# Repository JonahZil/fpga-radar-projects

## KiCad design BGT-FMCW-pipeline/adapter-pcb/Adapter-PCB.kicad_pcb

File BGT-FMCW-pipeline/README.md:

# FPGA FMCW Radar Pipeline

This project implements a complete real-time radar system using an Infineon BGT60TR13C shield radar sensor and a Xilinx Zynq-7000 SoC. The radar detects the strongest object in front of it, calculates its distance and direction on the FPGA, and sends the resulting 3D position to a Python application for visualization. The demonstration below shows the system tracking a moving corner reflector.

## Overview

The complete processing chain is:

BGT60TR13C
    -> Radar configuration
    -> SPI acquisition
    -> three-channel buffering
    -> Hann windowing
    -> three 256-point range FFTs, built from scratch
    -> strongest-target detection
    -> range and angle calculation
    -> AXI4-Lite
    -> Zynq processing system
    -> UART
    -> Python 3D visualization

Nearly all radar processing is performed in programmable logic. The processing system only reads the completed result and forwards it to the computer over UART.

## Hardware

The system consists of:

* Infineon BGT60TR13C 60 GHz FMCW radar shield
* Zybo Z7 with a Xilinx Zynq-7000 SoC
* Custom radar-to-PMOD adapter PCB
* Three radar receiver channels and one transmitter
* USB UART connection to the computer

The radar operates with 1.8 V logic, while the Zybo PMOD uses 3.3 V logic. The custom PCB uses two SN74AVC4T245 level translators and an AP2112K 1.8 V regulator to safely connect the boards. The adapter PCB is shown below:

## Radar Configuration

The FPGA configures the BGT60TR13C through SPI using register values stored in a ROM. It starts each frame, waits for the sensor FIFO interrupt, and performs a burst read of the ADC samples.

The current configuration uses:

* Three receiver channels
* 256 samples per receiver
* 768 ADC samples per frame
* 256-point range FFTs
* FFT bins 6 through 127 for target detection
* 37.5 mm of range per FFT bin
* A 100 MHz FPGA clock
* A frame period of approximately 16.7 ms
* An update rate of approximately 60 FPS

## Signal Processing

### Acquisition and Buffering

The BGT60TR13C produces interleaved 12-bit unsigned ADC samples from its three receiver channels. The FPGA reads the FIFO over SPI, separates the channels, subtracts the ADC midpoint of 2048, and stores each channel in BRAM.

### Hann Window

A 256-point Hann window is applied before each FFT to reduce spectral leakage. The coefficients are stored in ROM as unsigned Q0.12 values.

### Range FFT

A separate 256-point fixed-point FFT is calculated for each receiver. Only positive-frequency bins 6 through 127 are searched. The lowest bins are ignored because they primarily contain DC leakage and direct coupling. The FFT module was made from scratch in the previous project, found under the "simulated-FMCW-pipeline" repository.

### Peak Detection

For each candidate bin, the design calculates:

power = real^2 + imaginary^2

The power values from all three receivers are added together. The bin with the largest combined response is selected as the strongest target.

### Range Calculation

Range is calculated directly from the selected FFT bin:

range_um = peak_bin * 37,500

The FPGA outputs range as an unsigned 24-bit integer in micrometres.

### Angle Calculation

Azimuth and elevation are calculated from the phase differences between the complex FFT outputs of different receiver pairs.

The design:

1. Multiplies one receiver value by the complex conjugate of another
2. Uses a custom CORDIC atan2 module to calculate the phase difference
3. Applies experimentally measured boresight phase offsets
4. Uses an inverse-sine lookup table to calculate the final angle

Phase and angle values use signed radians scaled by 2^15.

The inverse-sine ROM discards seven least-significant phase bits before lookup:

lut_address = abs(corrected_phase) >> 7

This reduces the ROM to 805 entries while retaining angular resolution.

The final RTL outputs are:

output reg signed [17:0] alpha;
output reg signed [17:0] beta;
output reg        [23:0] range_calc;

* alpha is the azimuth in radians multiplied by 2^15
* beta is the elevation in radians multiplied by 2^15
* range_calc is the range in micrometres

## Data Transfer and Visualization

The completed results are exposed to the Zynq processing system through a custom AXI4-Lite peripheral using the Vivado AXI4-Lite template.

Embedded C software waits for a valid result, reads the three output registers, and sends them over UART at 921,600 baud.

Each packet contains:

uint32 range_um
int32  alpha_q15
int32  beta_q15

The Python application decodes the packet, converts the fixed-point values to metres and degrees, transforms the spherical coordinates into Cartesian coordinates, and updates a Matplotlib 3D display.

The current implementation displays one point because the FPGA returns only the strongest target.

## Fixed-Point Formats

The main fixed-point formats are:

* Raw ADC sample: 12-bit unsigned integer
* Centered ADC sample: signed integer
* Hann coefficient: unsigned Q0.12
* FFT input: 24-bit signed with 15 fractional bits
* FFT real and imaginary outputs: 24-bit signed
* Phase: signed radians multiplied by 2^15
* Azimuth and elevation: signed radians multiplied by 2^15
* Range: unsigned integer, micrometres

Intermediate calculations use wider values to prevent overflow before truncation.

## Main RTL Modules

* bgt_master: radar configuration and acquisition state machine
* spi_master: radar register transactions
* burst_spi_master: continuous FIFO burst reads
* config_rom: BGT60TR13C register configuration
* io_buffer: buffering and signal-processing control
* hann_rom: Hann-window coefficients
* sdf_fft: three 256-point range FFTs
* atan2_cordic: phase-difference calculation
* cordic_angle_rom: CORDIC constants
* asin_rom: phase-to-angle conversion
* AXI4-Lite slave: transfers completed results to the processing system

## FPGA Implementation

The design meets timing at 100 MHz with a worst negative slack of **+0.428 ns**.

Resource utilization:

* LUT: 5,689 used, 32%
* Flip-flops: 5,418 used, 15%
* BRAM: 14.5 blocks used, 24%
* DSP slices: 50 used, 63%

DSP slices are the most heavily used resource because of the FFTs, window multiplication, magnitude calculations, and complex phase arithmetic.

## Verification

The pipeline was verified using:

* RTL simulation
* Python and NumPy reference calculations
* Synthetic ADC signals with known frequencies and phase offsets
* Vivado ILA and VIO
* Comparison of FPGA FFT outputs with software FFTs
* Fixed-point range and angle comparisons
* Physical testing with a corner reflector
* Measurements at boresight and different target distances

The Python reference model reproduces the same fixed-point scaling and seven-bit phase truncation used by the RTL.

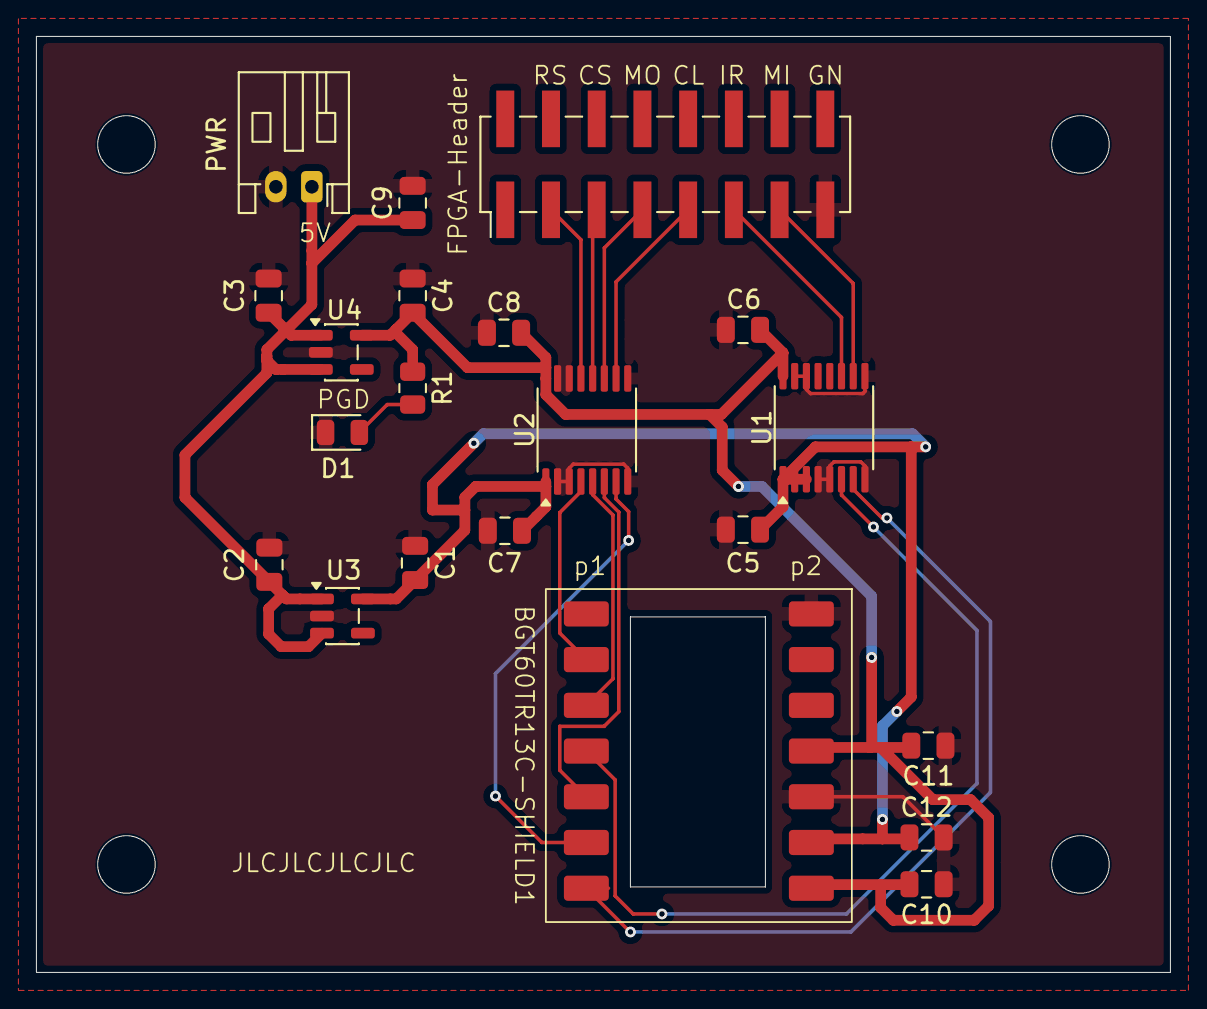
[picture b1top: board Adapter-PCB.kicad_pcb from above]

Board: 2 copper layers, 63.0 x 52.0 mm, 21 parts (0 on the bottom side), 17 nets.

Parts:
BGT60TR13C-SHIELD1: BGT60TR13C-SHIELD
C1, C2, C3, C4, C11: 10 µF; C_0805_2012Metric
C5, C6, C7, C8, C10, C12: 100 nF; C_0805_2012Metric
C9: 22 µF; C_0805_2012Metric
D1: LED; LED_0805_2012Metric
FPGA-Header: Conn_02x08_Odd_Even; PinHeader_2x08_P2.54mm_Vertical_SMD
PWR: 5V; JST_PH_S2B-PH-K_1x02_P2.00mm_Horizontal
R1: 1k; R_0805_2012Metric
U1, U2: SN74AVC4T245PW; TSSOP-16_4.4x5mm_P0.65mm
U3: AP2112K-1.8; SOT-23-5
U4: AP2112K-3.3; SOT-23-5

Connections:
+5V: C2.2, C3.2, C9.1, PWR.1, U3.1 (VIN), U3.3 (EN), U4.1 (VIN), U4.3 (EN)
GND: BGT60TR13C-SHIELD1.8 (GND), BGT60TR13C-SHIELD1.12 (GND), C1.1, C2.1, C3.1, C4.1, C5.1, C6.1, C7.1, C8.1, C9.2, C10.1, C11.1, C12.2, D1.1 (K), FPGA-Header.15, PWR.2, U1.4 (1A1), U1.5 (1A2), U1.8 (GND), U1.9 (GND), U1.14 (2~OE), U1.15 (1~OE), U2.2 (1DIR), U2.3 (2DIR), U2.8 (GND), U2.9 (GND), U2.14 (2~OE), U2.15 (1~OE), U3.2 (GND), U4.2 (GND)
unnamed: BGT60TR13C-SHIELD1.13 (1V8S), C1.2, C5.2, C7.2, C12.1, U1.1 (VCCA), U1.2 (1DIR), U1.3 (2DIR), U2.1 (VCCA), U3.5 (VOUT)
unnamed: BGT60TR13C-SHIELD1.11 (3V3D), BGT60TR13C-SHIELD1.14 (3V3S), C4.2, C6.2, C8.2, C10.2, C11.2, R1.1, U1.16 (VCCB), U2.16 (VCCB), U4.5 (VOUT)
unnamed: BGT60TR13C-SHIELD1.7 (IRQ), U1.7 (2A2)
unnamed: BGT60TR13C-SHIELD1.2 (RST), U2.4 (1A1)
unnamed: BGT60TR13C-SHIELD1.6 (SPI_CLK), U2.7 (2A2)
unnamed: BGT60TR13C-SHIELD1.3 (SPI_CSN), U2.5 (1A2)
unnamed: BGT60TR13C-SHIELD1.4 (SPI_MISO), U1.6 (2A1)
unnamed: BGT60TR13C-SHIELD1.5 (SPI_MOSI), U2.6 (2A1)
unnamed: D1.2 (A), R1.2
unnamed: FPGA-Header.3, U2.13 (1B1)
unnamed: FPGA-Header.5, U2.12 (1B2)
unnamed: FPGA-Header.7, U2.11 (2B1)
unnamed: FPGA-Header.9, U2.10 (2B2)
unnamed: FPGA-Header.11, U1.11 (2B1)
unnamed: FPGA-Header.13, U1.10 (2B2)

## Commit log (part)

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2026-02-28 Initial commit of all code files
2026-03-02 Started 32 point SDF FFT project. Implemented a more efficient streaming butterfly module.
2026-03-04 Added the delay line module
2026-03-04 Added stage module, have not implemented timings or logic yet
2026-03-05 Added logic for stage_module, no twiddle yet
2026-03-07 Added a basic testbench, need to debug butterfly module
2026-03-10 Fixed timing issue with butterfly module
2026-03-24 Fixed allignment issues in stage module, now works. Missing twiddle factors
2026-03-31 Made the SDF fully functional with 8 points
2026-03-31 Added a readme file for the project
2026-04-01 Added the 32 point FFT FPGA pipeline, though bugs appear in the delay line.
2026-04-01 Added the python file to calculate the twiddle factors for the twiddle ROMs
2026-04-03 Made the delay line synchronous, has not fixed issues yet
2026-05-06 Final commit of 32 point SDF FFT, fully functional
2026-05-06 Commit of 32 point SDF FFT pipeline files
2026-05-06 Added readme file
2026-05-06 Added readme file for 32 point SDF pipeline
2026-05-06 Added diagram to README file
2026-05-07 Temporary files for 128 point FFT
2026-05-07 Final public commit of files
2026-05-07 Added detailed README file and the simulated FMCW radar model
2026-05-07 Updated README file with captions
2026-05-09 Cleaned up the README files
2026-05-09 Cleaned up README files
2026-06-25 Added files for BGT pipeline
